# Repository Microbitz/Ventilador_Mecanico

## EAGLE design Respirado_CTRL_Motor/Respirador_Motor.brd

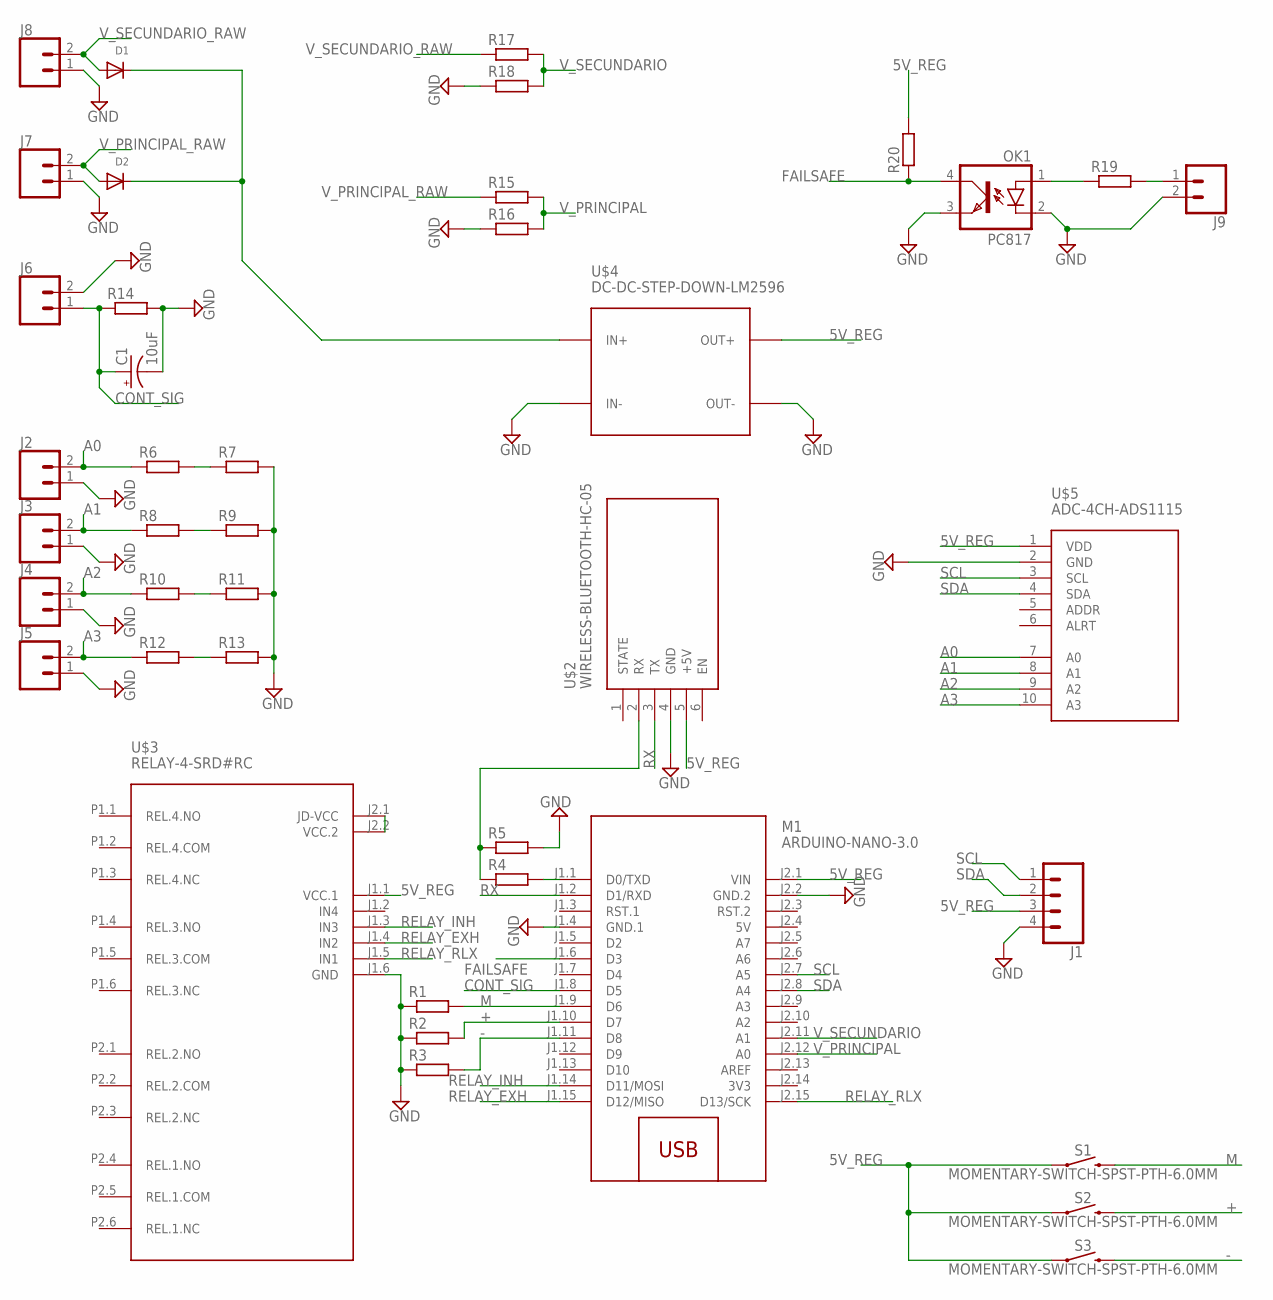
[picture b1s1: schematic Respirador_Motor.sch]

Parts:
C1: 10uF; EIA3216
D1, D2: DIODEDO-1N4148; DO-1N4148
J1: CONN_04; 1X04
J2, J3, J4, J5, J6, J7, J8, J9: CONN_025MM; SCREWTERMINAL-5MM-2
M1: ARDUINO-NANO-3.0
OK1: PC817; DIL04
R1, R2, R3, R4, R5, R6, R7, R8, R9, R10, R11, R12, R13, R14, R15, R16, R17, R18, R19, R20: R-EU_0207/10; 0207/10
S1, S2, S3: MOMENTARY-SWITCH-SPST-PTH-6.0MM; TACTILE_SWITCH_PTH_6.0MM
U$2: WIRELESS-BLUETOOTH-HC-05
U$3: RELAY-4-SRD#RC
U$4: DC-DC-STEP-DOWN-LM2596
U$5: ADC-4CH-ADS1115

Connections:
3V3: M1.J2.14 (3V3)
5V: M1.J2.4 (5V)
5V_REG: J1.3, M1.J2.1 (VIN), R20.2, S1.1, S2.1, S3.1, U$2.5 (+5V), U$3.J1.1 (VCC.1), U$4.OUT+, U$5.1 (VDD)
+: M1.J1.10 (D7), R2.2, S2.3 (2)
-: M1.J1.11 (D8), R3.2, S3.3 (2)
A0: J2.2, R6.1, U$5.7 (A0)
A1: J3.2, R8.1, U$5.8 (A1)
A2: J4.2, R10.1, U$5.9 (A2)
A3: J5.2, R12.1, U$5.10 (A3)
CONT_SIG: C1.A (+), J6.1, M1.J1.8 (D5), R14.1
FAILSAFE: M1.J1.6 (D3), OK1.4 (COL), R20.1
GND: C1.C (-), J1.4, J2.1, J3.1, J4.1, J5.1, J6.2, J7.1, J8.1, J9.2, M1.J1.4 (GND.1), M1.J2.2 (GND.2), OK1.2 (C), OK1.3 (EMIT), R1.1, R2.1, R3.1, R5.2, R7.2, R9.2, R11.2, R13.2, R14.2, R16.1, R18.1, U$2.4 (GND), U$3.J1.6 (GND), U$4.IN-, U$4.OUT-, U$5.2 (GND)
M: M1.J1.9 (D6), R1.2, S1.3 (2)
unnamed: R6.2, R7.1
unnamed: R8.2, R9.1
unnamed: R10.2, R11.1
unnamed: M1.J1.1 (D0/TXD), R4.2
unnamed: R12.2, R13.1
unnamed: J9.1, R19.2
unnamed: D1.C, D2.C, U$4.IN+
unnamed: R4.1, R5.1, U$2.2 (RX)
unnamed: U$3.J2.1 (JD-VCC), U$3.J2.2 (VCC.2)
unnamed: OK1.1 (A), R19.1
RELAY_EXH: M1.J1.15 (D12/MISO), U$3.J1.4 (IN2)
RELAY_INH: M1.J1.14 (D11/MOSI), U$3.J1.3 (IN3)
RELAY_RLX: M1.J2.15 (D13/SCK), U$3.J1.5 (IN1)
RX: M1.J1.2 (D1/RXD), U$2.3 (TX)
SCL: J1.1, M1.J2.7 (A5), U$5.3 (SCL)
SDA: J1.2, M1.J2.8 (A4), U$5.4 (SDA)
V_PRINCIPAL: M1.J2.12 (A0), R15.2, R16.2
V_PRINCIPAL_RAW: D2.A, J7.2, R15.1
V_SECUNDARIO: M1.J2.11 (A1), R17.2, R18.2
V_SECUNDARIO_RAW: D1.A, J8.2, R17.1

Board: 2 copper layers, 41 parts (0 on the bottom side), 31 nets, no tracks yet.

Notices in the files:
parts and their libraries:
diy-modules: Released under the Creative Commons Attribution 4.0 International License: http://creativecommons.org/licenses/by/4.0
SparkFun-Connectors: Licensing: Creative Commons ShareAlike 4.0 International - https://creativecommons.org/licenses/by-sa/4.0
